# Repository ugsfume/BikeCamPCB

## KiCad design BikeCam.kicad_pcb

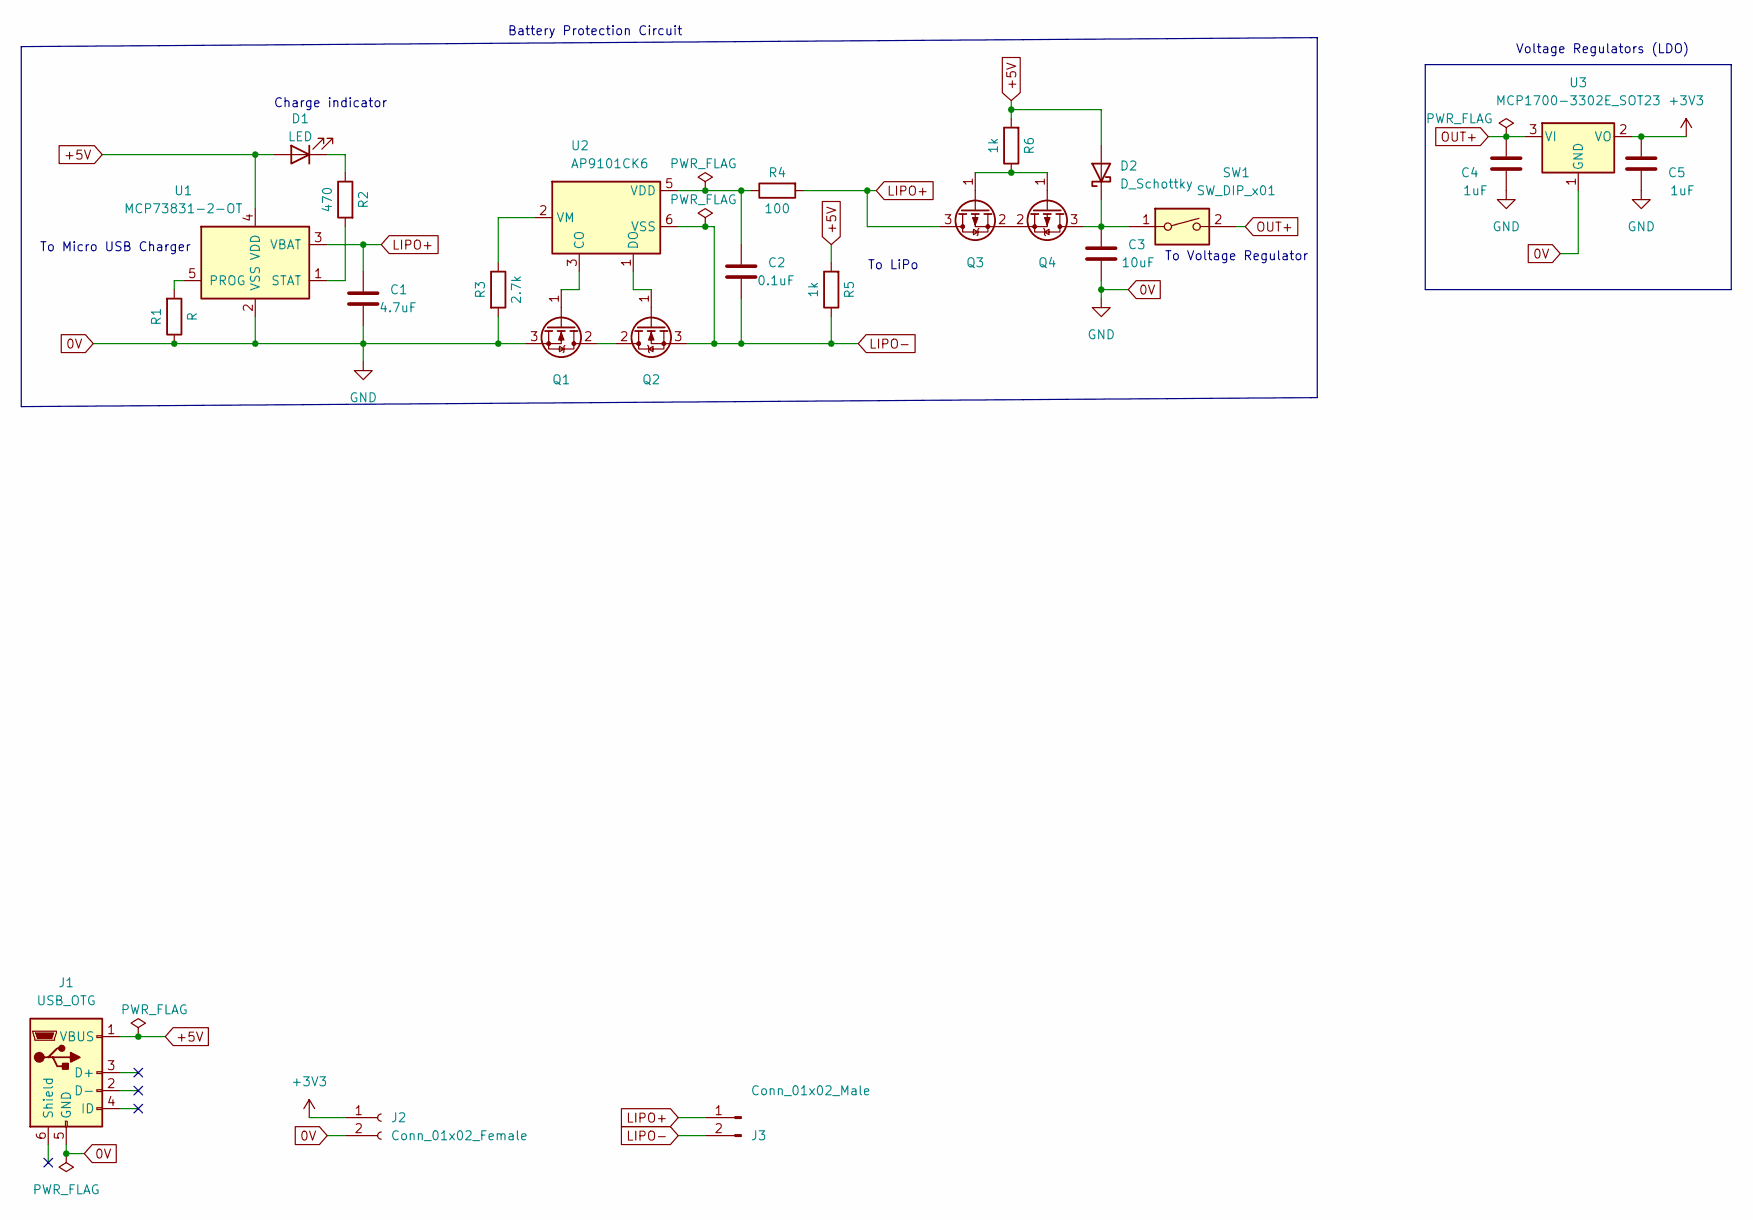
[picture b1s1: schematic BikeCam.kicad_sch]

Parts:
C1: 4.7uF; C_0402_1005Metric
C2: 0.1uF; C_0402_1005Metric
C3: 10uF; C_0402_1005Metric
C4, C5: 1uF; C_0402_1005Metric
D1: LED; LED_1206_3216Metric
D2: D_Schottky; D_DO-41_SOD81_P2.54mm_Vertical_AnodeUp
J1: USB_OTG; USB_Micro-B_GCT_USB3076-30-A
J2: Conn_01x02_Female; PinSocket_1x02_P2.00mm_Vertical
J3: Conn_01x02_Male; PinHeader_1x02_P2.00mm_Vertical
Q1, Q2: IRLZ34N; SOT-23
Q3, Q4: IRLML5203; SOT-23
R1: R; R_0805_2012Metric_Pad1.20x1.40mm_HandSolder
R2: 470; R_0805_2012Metric_Pad1.20x1.40mm_HandSolder
R3: 2.7k; R_0805_2012Metric_Pad1.20x1.40mm_HandSolder
R4: 100; R_0805_2012Metric_Pad1.20x1.40mm_HandSolder
R5, R6: 1k; R_0805_2012Metric_Pad1.20x1.40mm_HandSolder
SW1: SW_DIP_x01; PinHeader_1x02_P2.00mm_Vertical
U1: MCP73831-2-OT; SOT-23-5
U2: AP9101CK6; SOT-23-6
U3: MCP1700-3302E_SOT23; SOT-23

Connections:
0V: C1.1, C3.1, C4.1, C5.1, J1.5 (GND), J2.2, Q1.3 (S), R1.1, R3.2, U1.2 (VSS), U3.1 (GND)
+3V3: C5.2, J2.1, U3.2 (VO)
+5V: D1.2 (A), D2.2 (A), J1.1 (VBUS), R5.2, R6.2, U1.4 (VDD)
LIPO+: C1.2, J3.1, Q3.3 (D), R4.2, U1.3 (VBAT)
LIPO-: C2.1, J3.2, Q2.3 (S), R5.1, U2.6 (VSS)
unnamed: C2.2, R4.1, U2.5 (VDD)
unnamed: C3.2, D2.1 (K), Q4.3 (D), SW1.1
unnamed: D1.1 (K), R2.1
unnamed: Q1.1 (G), U2.3 (CO)
unnamed: Q1.2 (D), Q2.2 (D)
unnamed: Q2.1 (G), U2.1 (DO)
unnamed: Q3.1 (G), Q4.1 (G), R6.1
unnamed: Q3.2 (S), Q4.2 (S)
unnamed: R1.2, U1.5 (PROG)
unnamed: R2.2, U1.1 (STAT)
unnamed: R3.1, U2.2 (VM)
OUT+: C4.2, SW1.2, U3.3 (VI)

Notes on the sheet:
Battery Protection Circuit
To LiPo
To Voltage Regulator
Charge indicator
Voltage Regulators (LDO)
To Micro USB Charger

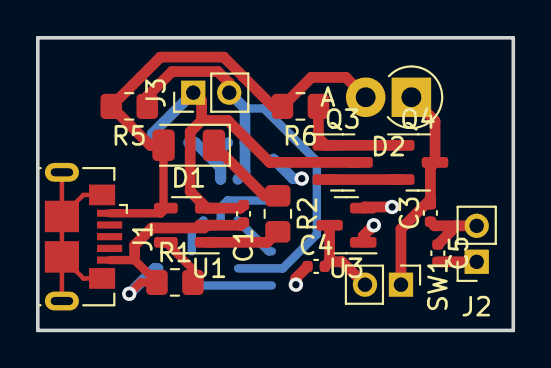
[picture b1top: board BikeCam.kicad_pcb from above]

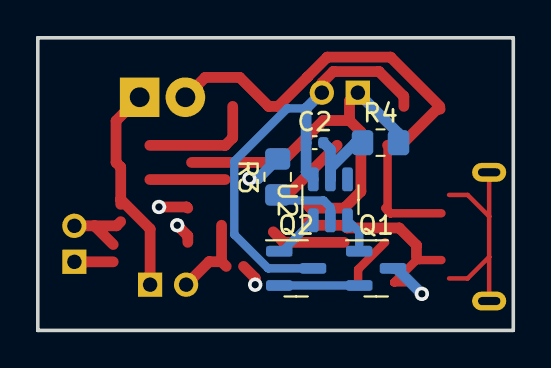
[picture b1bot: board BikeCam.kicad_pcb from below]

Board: 4 copper layers, 26.4 x 16.3 mm, 24 parts (6 on the bottom side), 17 nets.

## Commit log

2023-02-16 schematic
2023-02-16 pcb trace
2023-02-17 pwr module debugging
2023-02-17 error debug
